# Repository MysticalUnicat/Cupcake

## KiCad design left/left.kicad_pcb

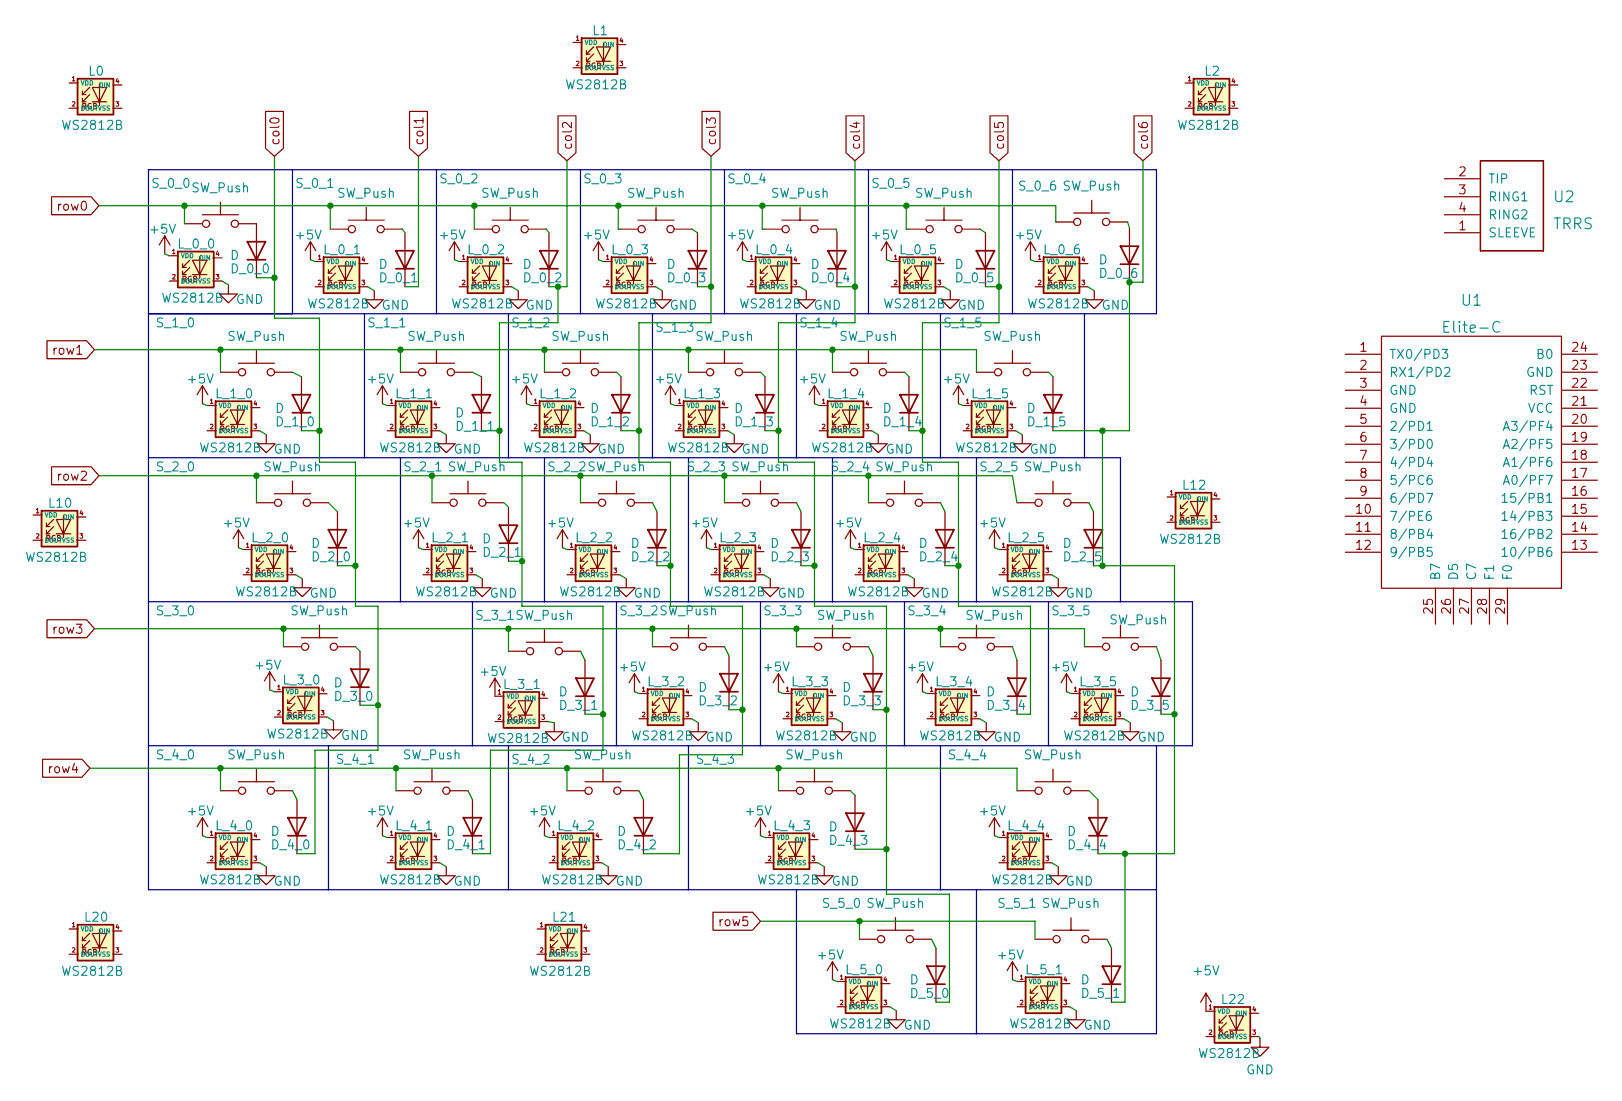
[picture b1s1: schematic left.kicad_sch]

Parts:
D_0_0, D_0_1, D_0_2, D_0_3, D_0_4, D_0_5, D_0_6: D; D_SOD-323
D_1_0, D_1_1, D_1_2, D_1_3, D_1_4, D_1_5, D_2_0, D_2_1, D_2_2, D_2_3, D_2_4, D_2_5, D_3_0, D_3_1, D_3_2, D_3_3, D_3_4, D_3_5, D_4_0, D_4_1, D_4_2, D_4_3, D_4_4, D_5_0, D_5_1: D; Diode
L0, L1, L2, L10, L12, L20, L21, L22: WS2812B; SK6812-MINI-E
L_0_0, L_0_1, L_0_2, L_0_3, L_0_4, L_0_5, L_0_6, L_1_0, L_1_1, L_1_2, L_1_3, L_1_4, L_1_5, L_2_0, L_2_1, L_2_2, L_2_3, L_2_4, L_2_5, L_3_0, L_3_1, L_3_2, L_3_3, L_3_4, L_3_5, L_4_0, L_4_1, L_4_2, L_4_3, L_4_4, L_5_0, L_5_1: WS2812B; SK6812-MINI-E
S_0_0, S_0_1, S_0_2, S_0_3, S_0_4, S_0_5, S_0_6, S_1_1, S_1_2, S_1_3, S_1_4, S_1_5, S_2_1, S_2_2, S_2_3, S_2_4, S_2_5, S_3_1, S_3_2, S_3_3, S_3_4, S_3_5: SW_Push; MXOnly-1U-Hotswap
S_1_0, S_4_4: SW_Push; MXOnly-1.5U-Hotswap
S_2_0, S_4_3: SW_Push; MXOnly-1.75U-Hotswap
S_3_0: SW_Push; MXOnly-2.25U-Hotswap
S_4_0, S_4_1, S_4_2, S_5_0, S_5_1: SW_Push; MXOnly-1.25U-Hotswap
U1: Elite-C
U2: TRRS

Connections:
+5V: L22.1 (VDD), L_0_0.1 (VDD), L_0_1.1 (VDD), L_0_2.1 (VDD), L_0_3.1 (VDD), L_0_4.1 (VDD), L_0_5.1 (VDD), L_0_6.1 (VDD), L_1_0.1 (VDD), L_1_1.1 (VDD), L_1_2.1 (VDD), L_1_3.1 (VDD), L_1_4.1 (VDD), L_1_5.1 (VDD), L_2_0.1 (VDD), L_2_1.1 (VDD), L_2_2.1 (VDD), L_2_3.1 (VDD), L_2_4.1 (VDD), L_2_5.1 (VDD), L_3_0.1 (VDD), L_3_1.1 (VDD), L_3_2.1 (VDD), L_3_3.1 (VDD), L_3_4.1 (VDD), L_3_5.1 (VDD), L_4_0.1 (VDD), L_4_1.1 (VDD), L_4_2.1 (VDD), L_4_3.1 (VDD), L_4_4.1 (VDD), L_5_0.1 (VDD), L_5_1.1 (VDD)
GND: L22.3 (VSS), L_0_0.3 (VSS), L_0_1.3 (VSS), L_0_2.3 (VSS), L_0_3.3 (VSS), L_0_4.3 (VSS), L_0_5.3 (VSS), L_0_6.3 (VSS), L_1_0.3 (VSS), L_1_1.3 (VSS), L_1_2.3 (VSS), L_1_3.3 (VSS), L_1_4.3 (VSS), L_1_5.3 (VSS), L_2_0.3 (VSS), L_2_1.3 (VSS), L_2_2.3 (VSS), L_2_3.3 (VSS), L_2_4.3 (VSS), L_2_5.3 (VSS), L_3_0.3 (VSS), L_3_1.3 (VSS), L_3_2.3 (VSS), L_3_3.3 (VSS), L_3_4.3 (VSS), L_3_5.3 (VSS), L_4_0.3 (VSS), L_4_1.3 (VSS), L_4_2.3 (VSS), L_4_3.3 (VSS), L_4_4.3 (VSS), L_5_0.3 (VSS), L_5_1.3 (VSS)
unnamed: D_0_0.2 (A), S_0_0.2
unnamed: D_0_1.2 (A), S_0_1.2
unnamed: D_0_2.2 (A), S_0_2.2
unnamed: D_0_3.2 (A), S_0_3.2
unnamed: D_0_4.2 (A), S_0_4.2
unnamed: D_0_5.2 (A), S_0_5.2
unnamed: D_0_6.2 (A), S_0_6.2
unnamed: D_1_0.2 (A), S_1_0.2
unnamed: D_1_1.2 (A), S_1_1.2
unnamed: D_1_2.2 (A), S_1_2.2
unnamed: D_1_3.2 (A), S_1_3.2
unnamed: D_1_4.2 (A), S_1_4.2
unnamed: D_1_5.2 (A), S_1_5.2
unnamed: D_2_0.2 (A), S_2_0.2
unnamed: D_2_1.2 (A), S_2_1.2
unnamed: D_2_2.2 (A), S_2_2.2
unnamed: D_2_3.2 (A), S_2_3.2
unnamed: D_2_4.2 (A), S_2_4.2
unnamed: D_2_5.2 (A), S_2_5.2
unnamed: D_3_0.2 (A), S_3_0.2
unnamed: D_3_1.2 (A), S_3_1.2
unnamed: D_3_2.2 (A), S_3_2.2
unnamed: D_3_3.2 (A), S_3_3.2
unnamed: D_3_4.2 (A), S_3_4.2
unnamed: D_3_5.2 (A), S_3_5.2
unnamed: D_4_0.2 (A), S_4_0.2
unnamed: D_4_1.2 (A), S_4_1.2
unnamed: D_4_2.2 (A), S_4_2.2
unnamed: D_4_3.2 (A), S_4_3.2
unnamed: D_4_4.2 (A), S_4_4.2
unnamed: D_5_0.2 (A), S_5_0.2
unnamed: D_5_1.2 (A), S_5_1.2
col0: D_0_0.1 (K), D_1_0.1 (K), D_2_0.1 (K), D_3_0.1 (K), D_4_0.1 (K)
col1: D_0_1.1 (K)
col2: D_0_2.1 (K), D_1_1.1 (K), D_2_1.1 (K), D_3_1.1 (K), D_4_1.1 (K)
col3: D_0_3.1 (K), D_1_2.1 (K), D_2_2.1 (K), D_3_2.1 (K), D_4_2.1 (K)
col4: D_0_4.1 (K), D_1_3.1 (K), D_2_3.1 (K), D_3_3.1 (K), D_4_3.1 (K), D_5_0.1 (K)
col5: D_0_5.1 (K), D_1_4.1 (K), D_2_4.1 (K), D_3_4.1 (K)
col6: D_0_6.1 (K), D_1_5.1 (K), D_2_5.1 (K), D_3_5.1 (K), D_4_4.1 (K), D_5_1.1 (K)
row0: S_0_0.1, S_0_1.1, S_0_2.1, S_0_3.1, S_0_4.1, S_0_5.1, S_0_6.1
row1: S_1_0.1, S_1_1.1, S_1_2.1, S_1_3.1, S_1_4.1, S_1_5.1
row2: S_2_0.1, S_2_1.1, S_2_2.1, S_2_3.1, S_2_4.1, S_2_5.1
row3: S_3_0.1, S_3_1.1, S_3_2.1, S_3_3.1, S_3_4.1, S_3_5.1
row4: S_4_0.1, S_4_1.1, S_4_2.1, S_4_3.1, S_4_4.1
row5: S_5_0.1, S_5_1.1

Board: 2 copper layers, 106 parts (49 on the bottom side), 46 nets, no tracks yet.

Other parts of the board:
J1: AudioJack4; 4pin35mmAudio

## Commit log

2022-03-14 after many attempts
    we decided to use a prebuilt logic board for both sides! so we can hand wire the first version, then many a version with builtin logic. *sigh*
2022-03-15 first version to test print
2022-03-16 added base, pegs, well
2022-03-31 some state..
2022-03-31 ........ hide my shame
